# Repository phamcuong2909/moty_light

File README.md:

# moty_light
All design and code files for Moty Light module used in a Smart Home or IOT system

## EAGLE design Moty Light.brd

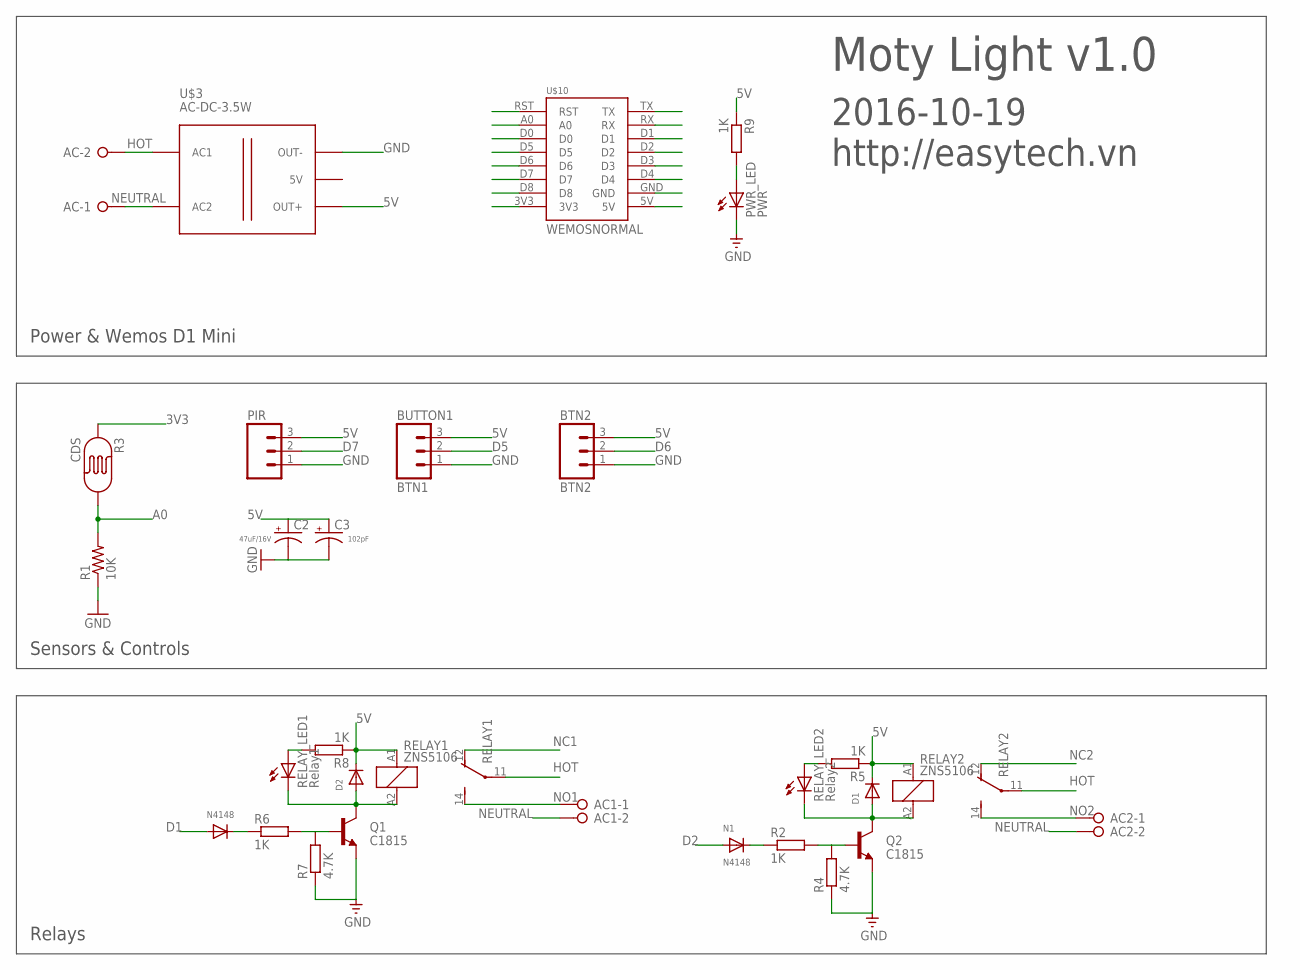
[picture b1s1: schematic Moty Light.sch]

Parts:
AC, AC1, AC2: W237-02P; W237-132
BTN2: BTN2; 1X03
BUTTON1: BTN1; 1X03
C2: 47uF/16V; CPOL-RADIAL-10UF-25V
C3: 102pF; CPOL-RADIAL-10UF-25V
D1, D2: DIODESMA; SMADIODE
N1: N4148; SOD-123
N4148: DIODESOD-123; SOD-123
PIR: M03PTH; 1X03
PWR_LED: PWR; LED3MM
Q1, Q2: C1815; SOT23-3
R1: 10K; R0805
R2, R5, R6, R8, R9: 1K; R0805
R3: CDS; PHOTOCELL_THIN
R4, R7: 4.7K; R0805
RELAY1, RELAY2: ZNS5106; ZN5
RELAY_LED1: Relay1; LED3MM
RELAY_LED2: Relay2; LED3MM
U$3: AC-DC-3.5W
U$10: WEMOSNORMAL; WEMOS

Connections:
3V3: R3.1, U$10.3V3
5V: BTN2.3, BUTTON1.3, C2.1 (+), C3.1 (+), D1.C, D2.C, PIR.3, R5.1, R8.1, R9.1, RELAY1.A1 (1), RELAY2.A1 (1), U$3.J2.3 (OUT+), U$10.5V
A0: R1.2, R3.2, U$10.A0
D0: U$10.D0
D1: N4148.A, U$10.D1
D2: N1.A, U$10.D2
D3: U$10.D3
D4: U$10.D4
D5: BUTTON1.2, U$10.D5
D6: BTN2.2, U$10.D6
D7: PIR.2, U$10.D7
D8: U$10.D8
GND: BTN2.1, BUTTON1.1, C2.2 (-), C3.2 (-), PIR.1, PWR_LED.K (C), Q1.2 (E), Q2.2 (E), R1.1, R4.1, R7.1, U$3.J2.1 (OUT-), U$10.GND
HOT: AC.2, RELAY1.11, RELAY2.11, U$3.J1.1 (AC1)
unnamed: D2.A, Q1.3 (C), RELAY1.A2 (2), RELAY_LED1.K (C)
unnamed: N4148.C, R6.1
unnamed: R8.2, RELAY_LED1.A
unnamed: D1.A, Q2.3 (C), RELAY2.A2 (2), RELAY_LED2.K (C)
unnamed: Q2.1 (B), R2.2, R4.2
unnamed: Q1.1 (B), R6.2, R7.2
unnamed: N1.C, R2.1
unnamed: R5.2, RELAY_LED2.A
unnamed: PWR_LED.A, R9.2
NC1: RELAY1.12 (O)
NC2: RELAY2.12 (O)
NEUTRAL: AC.1, AC1.2, AC2.2, U$3.J1.2 (AC2)
NO1: AC1.1, RELAY1.14 (S)
NO2: AC2.1, RELAY2.14 (S)
RST: U$10.RST
RX: U$10.RX
TX: U$10.TX

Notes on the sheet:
Moty Light v1.0
2016-10-19 http://easytech.vn
Power & Wemos D1 Mini
Sensors & Controls
Relays

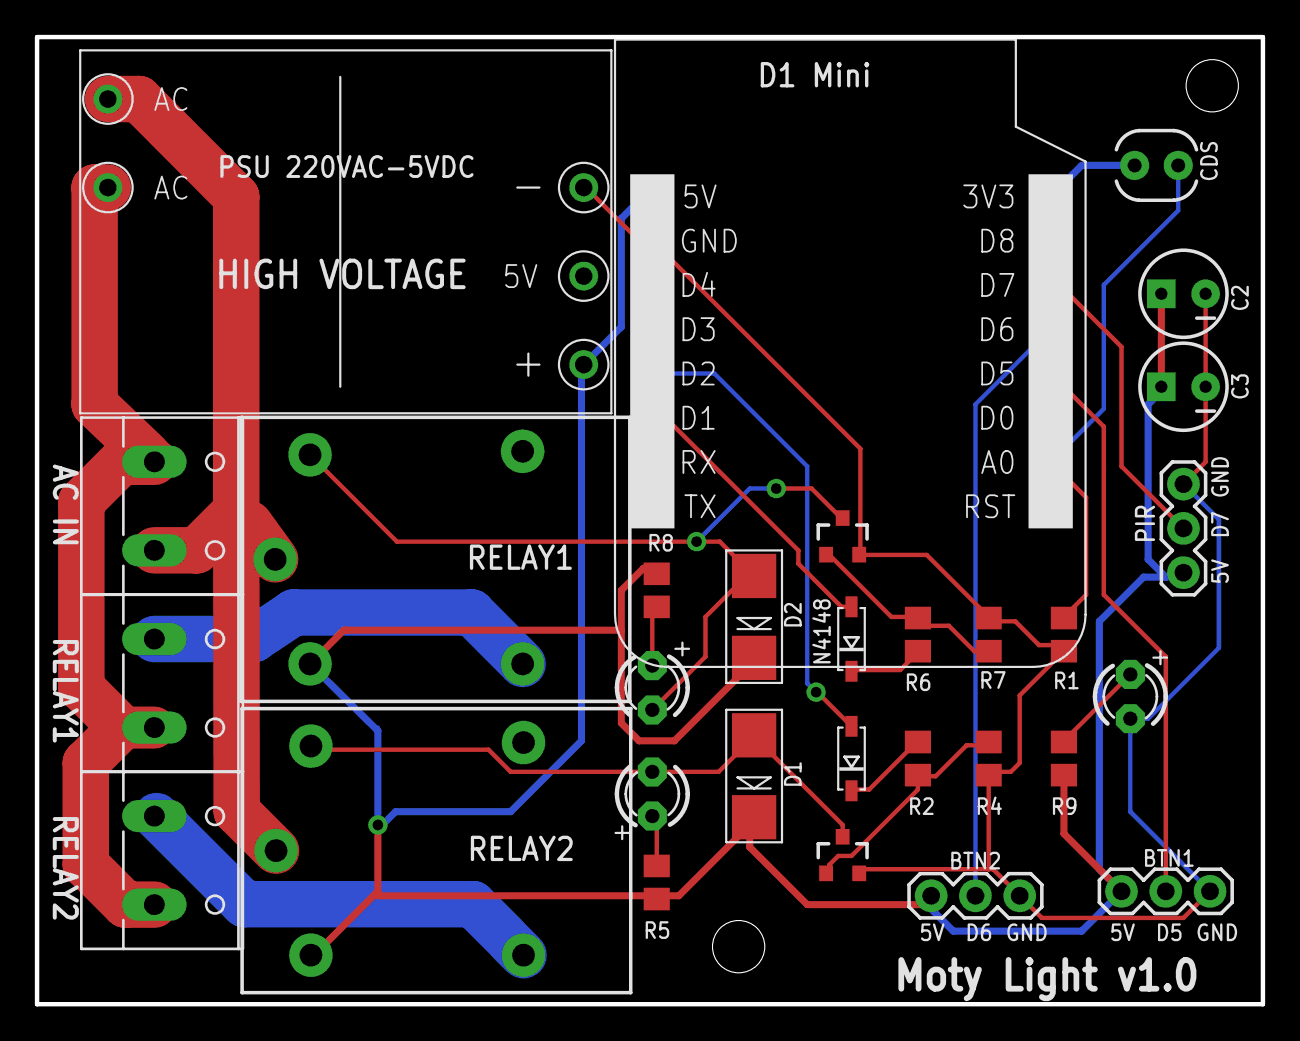
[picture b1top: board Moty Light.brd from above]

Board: 2 copper layers, 70.3 x 55.5 mm, 33 parts (1 on the bottom side), 22 nets.

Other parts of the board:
U$7, U$8: KFH-M3
U$17: ICON_EXL-S

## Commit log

2016-06-08 Initial checkin for sample code, design and rendered images
2016-08-28 Update to new version to match size of new box
2016-09-07 Update design to use SSR and fit in a box and update code to support view status and config via web
2016-11-02 Add gerber files and sample codes
2016-11-05 Update sample code
2016-12-27 Add sample code for moty light

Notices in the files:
parts and their libraries:
penn-engineering: Copyright (C) 2010, Bob Starr
dicons: Copyright (C) 2008, Bob Starr
SparkFun-Sensors: Licensing: Creative Commons ShareAlike 4.0 International - https://creativecommons.org/licenses/by-sa/4.0
